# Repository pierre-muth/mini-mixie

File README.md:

# mini-mixie
Resource about a small nixie Clock

The story is here https://pierremuth.wordpress.com/2018/07/30/glow-discharge-numeric-indicator-adventures/

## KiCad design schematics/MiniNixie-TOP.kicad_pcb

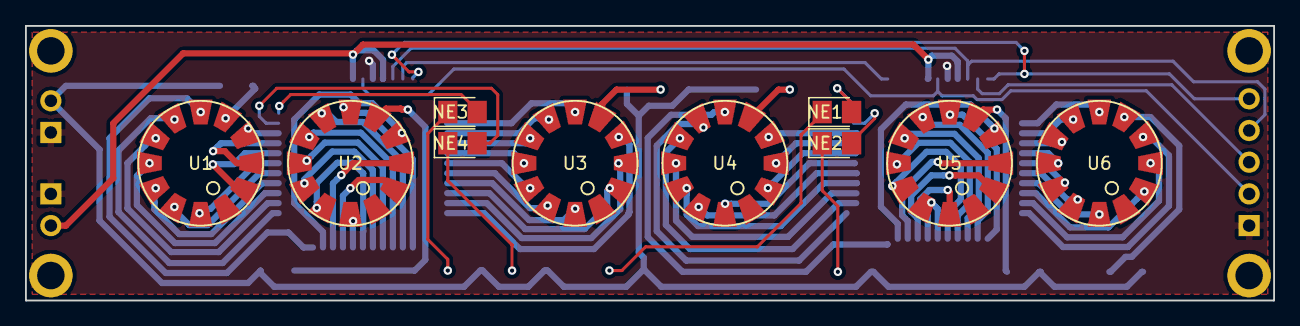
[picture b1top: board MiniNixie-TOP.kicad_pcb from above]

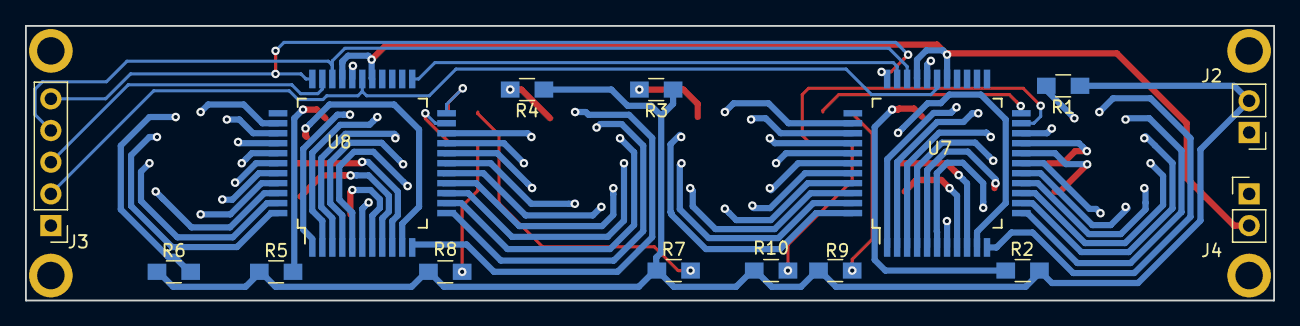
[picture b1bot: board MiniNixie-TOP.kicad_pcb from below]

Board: 2 copper layers, 100.0 x 22.0 mm, 25 parts (15 on the bottom side), 82 nets.

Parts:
J2, J4: Conn_01x02_Male; Pin_Header_Straight_1x02_Pitch2.54mm
J3: Conn_01x05_Male; Pin_Header_Straight_1x05_Pitch2.54mm
NE1, NE2, NE3, NE4: Lamp_Neon; CP_Tantalum_Case-R_EIA-2012-12_Reflow
R1, R2, R3, R4, R5, R6: 27K; R_0805_HandSoldering
R7, R8, R9, R10: 220K; R_0805_HandSoldering
U1, U2, U3, U4, U5, U6: LD8007
U7, U8: HV5522PG; PQFP-44_10x10mm_Pitch0.8mm

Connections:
+12V: J4.2, U7.27, U7.30, U8.27, U8.30
CLK: J3.2, U7.28, U8.28
DATA: J3.3, U8.32
GND: J2.1, J3.1, J4.1, U7.29, U8.29
HH0: U1.9, U7.20
HH1: U1.7, U7.11
HH2: U1.6, U7.12
HH3: U1.5, U7.13
HH4: U1.4, U7.14
HH5: U1.3, U7.15
HH6: U1.2, U7.16
HH7: U1.1, U7.17
HH8: U1.11, U7.18
HH9: U1.10, U7.19
HLP: NE3.2, U7.22
HM0: U3.9, U7.44
HM1: U3.7, U7.35
HM2: U3.6, U7.36
HM3: U3.5, U7.37
HM4: U3.4, U7.38
HM5: U3.3, U7.39
HM6: U3.2, U7.40
HM7: U3.1, U7.41
HM8: U3.11, U7.42
HM9: U3.10, U7.43
HRP: NE1.2, U8.22
HS0: U5.9, U8.10
HS1: U5.7, U8.1
HS2: U5.6, U8.2
HS3: U5.5, U8.3
HS4: U5.4, U8.4
HS5: U5.3, U8.5
HS6: U5.2, U8.6
HS7: U5.1, U8.7
HS8: U5.11, U8.8
HS9: U5.10, U8.9
HT: J2.2, R1.1, R2.1, R3.1, R4.1, R5.1, R6.1, R7.2, R8.2, R9.2, R10.2
LH0: U2.9, U7.10
LH1: U2.7, U7.1
LH2: U2.6, U7.2
LH3: U2.5, U7.3
LH4: U2.4, U7.4
LH5: U2.3, U7.5
LH6: U2.2, U7.6
LH7: U2.1, U7.7
LH8: U2.11, U7.8
LH9: U2.10, U7.9
LLP: NE4.2, U7.21
LM0: U4.9, U8.20
LM1: U4.7, U8.11
LM2: U4.6, U8.12
LM3: U4.5, U8.13
LM4: U4.4, U8.14
LM5: U4.3, U8.15
LM6: U4.2, U8.16
LM7: U4.1, U8.17
LM8: U4.11, U8.18
LM9: U4.10, U8.19
LRP: NE2.2, U8.21
LS0: U6.9, U8.44
LS1: U6.7, U8.35
LS2: U6.6, U8.36
LS3: U6.5, U8.37
LS4: U6.4, U8.38
LS5: U6.3, U8.39
LS6: U6.2, U8.40
LS7: U6.1, U8.41
LS8: U6.11, U8.42
LS9: U6.10, U8.43
unnamed: NE1.1, R7.1
unnamed: NE2.1, R8.1
unnamed: NE3.1, R9.1
unnamed: NE4.1, R10.1
unnamed: R1.2, U1.8
unnamed: R2.2, U2.8
unnamed: R3.2, U3.8
unnamed: R4.2, U4.8
unnamed: R5.2, U5.8
unnamed: R6.2, U6.8
unnamed: U7.32, U8.23
~BL: J3.5, U7.33, U8.33
~LE: J3.4, U7.31, U8.31

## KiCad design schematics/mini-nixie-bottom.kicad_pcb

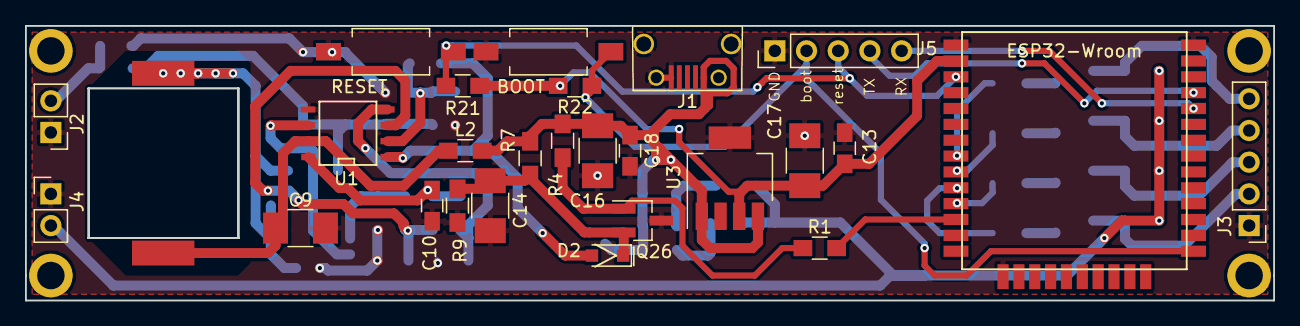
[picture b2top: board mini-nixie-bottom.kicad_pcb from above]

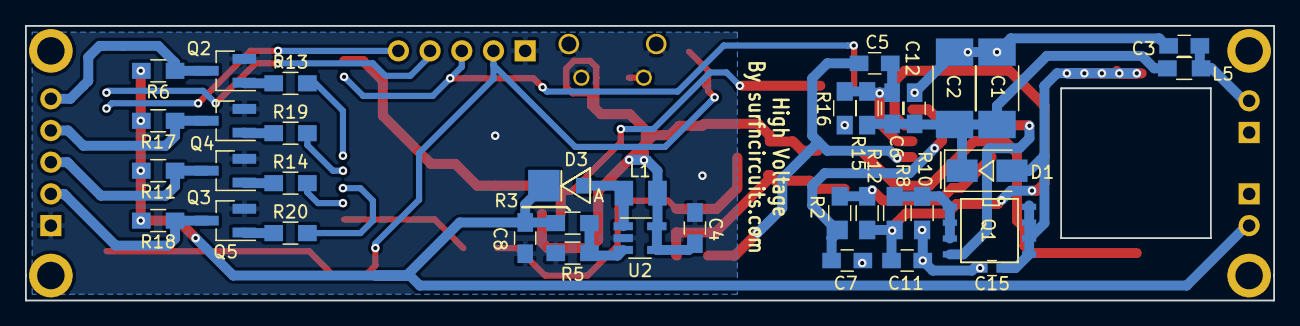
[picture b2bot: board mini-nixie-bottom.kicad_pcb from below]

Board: 2 copper layers, 100.0 x 22.0 mm, 64 parts (37 on the bottom side), 36 nets.

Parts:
BOOT: SW_Push; SW_SPST_EVQPE1
C1, C2: 1u 250V; C_1812_HandSoldering
C3, C12: 0.1u 250V; C_0805_HandSoldering
C4: 2.2u; C_0805_HandSoldering
C5: 220p; C_0805_HandSoldering
C6: 100p 250V; C_0805_HandSoldering
C7: 430p; C_0805_HandSoldering
C8: 10u; C_0805_HandSoldering
C9, C16: 100u 16V; C_1210_HandSoldering
C10: 0.1u 16V; C_0805_HandSoldering
C11: 1n; C_0805_HandSoldering
C13: 1u; C_0805_HandSoldering
C14: 47u 16V; C_1210_HandSoldering
C15: 560p 250V; C_0603_HandSoldering
C17: 100u; C_1210_HandSoldering
C18: 0.1u; C_0805_HandSoldering
D1: ES1D; D_SMA
D2: BAT54; D_SOD-323_HandSoldering
D3: MBRM140T3G
J1: USB_OTG; USB_Micro-B
J2, J4: Conn_01x02_Female; Pin_Header_Straight_1x02_Pitch2.54mm
J3, J5: Conn_01x05_Female; Pin_Header_Straight_1x05_Pitch2.54mm
L1: 10u; murata10uH
L2, L5: 60Ohm 100MHz; R_0805_HandSoldering
L3: 33u; WE33uHcut
Q1: FDS2672; SOIC-8-N
Q2, Q3, Q4, Q5: BSS138; SOT-23_Handsoldering
Q26: MMBTA42; SOT-23_Handsoldering
R1, R8: 1K; R_0805_HandSoldering
R2: 60.4K; R_0805_HandSoldering
R3: 40.2K; R_0805_HandSoldering
R4, R9: 100K; R_0805_HandSoldering
R5: 4.7K; R_0805_HandSoldering
R6, R11, R13, R14, R17, R18, R19, R20, R21, R22: 10K; R_0805_HandSoldering
R7: 2K; R_0805_HandSoldering
R10: 0.1 1/2W; R_0805_HandSoldering
R12: 4.12K; R_0805_HandSoldering
R15: 634K; R_0805_HandSoldering
R16: 7.68K; R_0805_HandSoldering
RESET: SW_Push; SW_SPST_EVQPE1
U1: UCC3803; SOIC-8-N
U2: MIC2288; SOT-23-5_HandSoldering
U3: LP38690; SOT-223-5
U4: ESP32-Wroom; ESP32-wroom

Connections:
+3V3: C13.1, C17.1, R21.2, R22.2, U3.3, U4.2
+5V: C4.1, C16.1, C18.1, J1.1, L1.2, L2.2, R4.1, R7.1, U2.4, U2.5, U3.1, U3.4
+12V: C8.1, D3.1, J4.2, R3.1, R6.2, R11.2, R17.2, R18.2
+170v: C3.1, J2.2, L5.1
BL: J3.5, Q2.3, R6.1
CLK: R20.2, U4.10
DATA: R14.2, U4.11
ESP_BOOT: BOOT.1, J5.2, R22.1, U4.25
ESP_EN: J5.3, R21.1, RESET.1, U4.3
ESP_RX: J5.5, U4.34
ESP_TX: J5.4, U4.35
GND: BOOT.2, C1.2, C2.2, C3.2, C4.2, C7.2, C8.2, C9.2, C10.2, C11.2, C12.2, C13.2, C14.2, C15.2, C16.2, C17.2, C18.2, J1.5, J1.6, J2.1, J3.1, J4.1, J5.1, Q2.2, Q3.2, Q4.2, Q5.2, Q26.3, R5.2, R9.2, R10.2, R16.2, RESET.2, U1.5, U2.2, U3.5, U4.1, U4.15, U4.38
LE: J3.4, Q4.3, R17.1
unnamed: C1.1, C2.1, C6.1, C12.1, D1.1, L5.2, R15.1
unnamed: C5.1, C6.2, R15.2, R16.1, U1.2
unnamed: C5.2, D2.2, U1.1
unnamed: C7.1, R2.2, U1.4
unnamed: C9.1, L2.1, L3.2, U1.7
unnamed: C10.1, R2.1, R12.2, U1.8
unnamed: C11.1, R8.2, R12.1, U1.3
unnamed: C14.1, D2.1, Q26.2, R7.2, R9.1
unnamed: C15.1, D1.2, L3.1, Q1.5, Q1.6, Q1.7, Q1.8
unnamed: D3.2, L1.1, U2.1
unnamed: Q1.1, Q1.2, Q1.3, R8.1, R10.1
unnamed: Q1.4, U1.6
unnamed: Q2.1, R13.1
unnamed: Q3.1, R14.1
unnamed: Q4.1, R19.1
unnamed: Q5.1, R20.1
unnamed: Q26.1, R1.1, R4.2
unnamed: R3.2, R5.1, U2.3
~BL: R13.2, U4.8
~CLK: J3.2, Q5.3, R18.1
~DATA: J3.3, Q3.3, R11.1
~HV_ENABLE: R1.2, U4.12
~LE: R19.2, U4.9

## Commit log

2020-03-31 add esp32 src
